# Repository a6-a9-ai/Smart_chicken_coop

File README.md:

# smartChicken: Multi-Sensor Environmental & Security System

A lightweight, event-driven application built on **Zephyr RTOS** for multi-sensor data collection and Bluetooth Low Energy (BLE) alert broadcasting.

## Project Structure
* **`soft_nRF`**: Core sensor hub firmware utilizing cooperative and preemptive workqueues to schedule non-blocking sensor sampling and manage UART/PWM peripherals.
* **`soft_nRF_R`**: Standalone receiver node logic that scans for specific broadcasting frames and drives physical LED indicators based on alert states.
* **`PCBs`**: Design files for 3 custom boards handling solar power adaptation, battery storage, and 3.3V/5V regulated power delivery.
* **`3D_prints`**: Mechanical manufacturing models, including a structural base support for a 24-cell PV solar panel.

---
<details>
  <summary> Power supply layout </summary>

</details>

<details>
  <summary> Receptor board layout </summary>

</details>

<details>
  <summary> Connector board layout </summary>

</details>

<details>
  <summary> Power supply routes </summary>

</details>

<details>
  <summary> Power supply 3D board </summary>

</details>

<details>
  <summary> Connector 3D board </summary>

</details>

<details>
  <summary> Receptor 3D board </summary>

</details>

## Technical Specifications

### 1. Concurrency Contexts (`main.c`)
The system offloads tasks to Zephyr's workqueue framework to avoid continuous thread shifting:
*   **`sensor_wq`**: Cooperative workqueue (Stack: 1024, Priority: 5) dedicated to regular, periodic sensor sampling routines.
*   **`critical_wq`**: Preemptive workqueue (Stack: 1024, Priority: -4) reserved for immediate actuator responses.

### 2. Peripheral & Sensor Matrix
*   **SCD30**: Interfaced via I2C (`DT_NODELABEL(scd30)`). It measures CO2, temperature, and humidity. Integrity is verified through a Sensirion-compliant polynomial `0x31` CRC-8 check.
*   **DHT11**: Connected via GPIO (`gpio0`, pin 4). Measures environmental metrics every 5000 ms using single-wire signaling.
*   **PIR Sensor**: Connected via GPIO (`gpio1`, pin 8). Polled asynchronously every 2500 ms to capture motion vectors.
*   **Photodiode**: Monitors ambient light variations.
*   **Fan Actuator**: Driven by hardware PWM (`DT_ALIAS(pwm_led0)`) with a baseline period of 40 µs.
*   **UART Host Link**: Mapped to `uart20` (RX: P1.05, TX: P1.04). Operates with a 4-byte receive buffer and a 1000 µs window timeout for ESP32 communications.

### 3. Thresholds & Control Hysteresis
*   **CO2 Threshold**: Registers an alert state if carbon dioxide levels exceed 1000.0 ppm.
*   **Fan & Thermal Management (`DHT11.c`)**:
    *   Turns **ON** (100% duty cycle) if Temperature > 23°C (`FAN_THRESHOLD_TEMP_SUP`).
    *   Turns **OFF** (0% duty cycle) when Temperature drops below 23°C.

### 4. Custom BLE Alert Protocol
The transmitting hub identifies itself as `"smartChicken"`. Discovered alerts modify a 1-byte payload packaged within a Custom Manufacturer Data sequence using Company ID `0x0D06`:

| Bit Index | Packet Macro Flag | Trigger Condition |
| :--- | :--- | :--- |
| **Bit 0** | `BLE_PAQUET_TEMP_BIT` | Temperature exceeds 23°C |
| **Bit 1** | `BLE_PAQUET_GAS_BIT` | SCD30 calculated CO2 exceeds 1000.0 ppm |
| **Bit 2** | `BLE_PAQUET_ATTACK_BIT` | Motion registered by the PIR sensor line |

The receiver application (`soft_nRF_R`) scans for this explicit frame, decodes the bit field state, and directly alters the status of `led0`, `led1`, and `led2`.

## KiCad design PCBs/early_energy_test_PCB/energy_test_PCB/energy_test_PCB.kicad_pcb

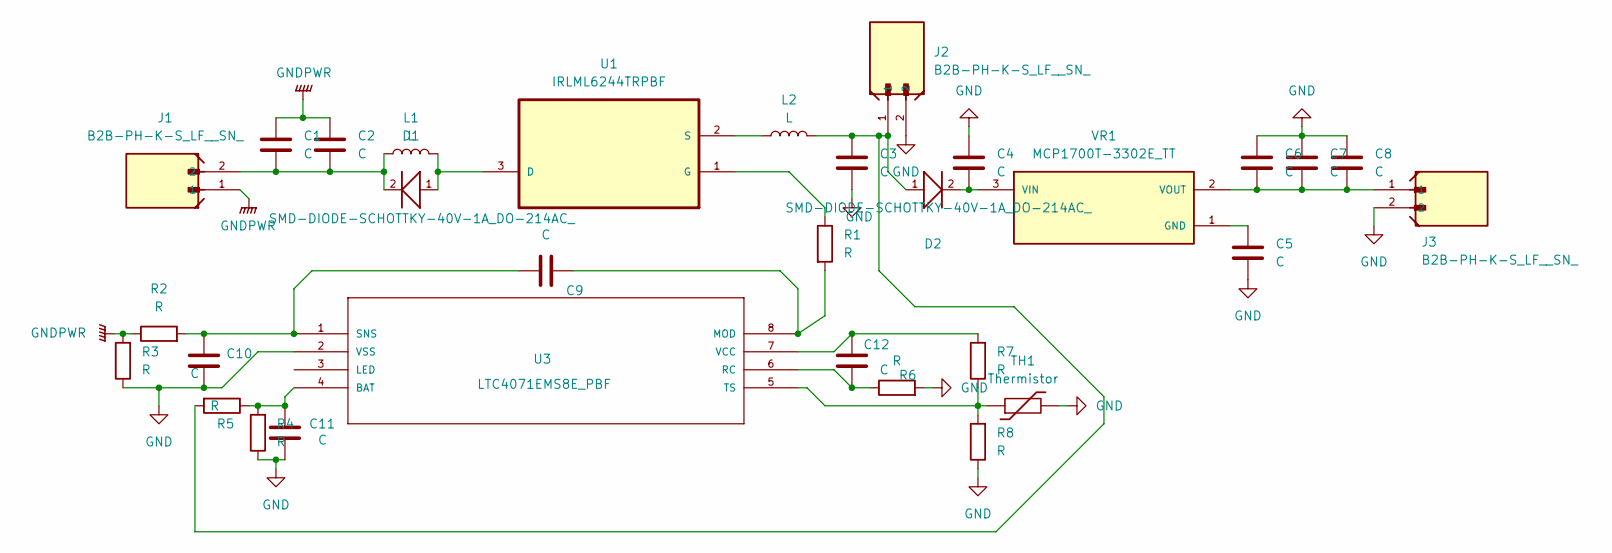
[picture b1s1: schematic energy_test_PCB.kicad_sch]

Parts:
C1, C2, C3, C4, C5, C6, C7, C8, C9, C10, C11, C12: C; R_Axial_DIN0207_L6.3mm_D2.5mm_P7.62mm_Horizontal
D1, D2: SMD-DIODE-SCHOTTKY-40V-1A_DO-214AC_; R_Axial_DIN0207_L6.3mm_D2.5mm_P7.62mm_Horizontal; MPN 1N5819
J1, J2, J3: B2B-PH-K-S_LF__SN_; JST_B2B-PH-K-S_LF__SN_
L1, L2: L; L_Radial_D12.0mm_P10.00mm_Neosid_SD12_style1
R1, R2, R3, R4, R5, R6, R7, R8: R; R_Axial_DIN0207_L6.3mm_D2.5mm_P7.62mm_Horizontal
TH1: Thermistor; R_Axial_DIN0207_L6.3mm_D2.5mm_P7.62mm_Horizontal
U1: IRLML6244TRPBF; SOT95P237X112-3N; MPN IRLML6244TRPBF
U3: LTC4071EMS8E_PBF; MSOP-8_MS; MANUFACTURER_PART_NUMBER ltc4071ems8e#pbf
VR1: MCP1700T-3302E_TT; SOT95P237X112-3N; PARTREV E

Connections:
GND: C3.2, C4.1, C5.2, C6.1, C7.1, C8.1, C10.1, C11.1, J2.2, J3.2, R3.1, R4.1, R6.2, R8.1, TH1.2, U3.2 (VSS)
GNDPWR: C1.1, C2.1, J1.1, R2.1, R3.2
unnamed: C1.2, C2.2, D1.2, J1.2, L1.1
unnamed: C3.1, D2.1, J2.1, L2.2, R5.2
unnamed: D1.1, L1.2, U1.3 (D)
unnamed: R1.1, U1.1 (G)
unnamed: L2.1, U1.2 (S)
unnamed: C11.2, R4.2, R5.1, U3.4 (BAT)
unnamed: C9.2, R1.2, U3.8 (MOD)
unnamed: C12.1, R6.1, U3.6 (RC)
unnamed: C9.1, C10.2, R2.2, U3.1 (SNS)
unnamed: R7.1, R8.2, TH1.1, U3.5 (TS)
unnamed: C12.2, R7.2, U3.7 (VCC)
unnamed: C5.1, VR1.1 (GND)
unnamed: C4.2, D2.2, VR1.3 (VIN)
unnamed: C6.2, C7.2, C8.2, J3.1, VR1.2 (VOUT)

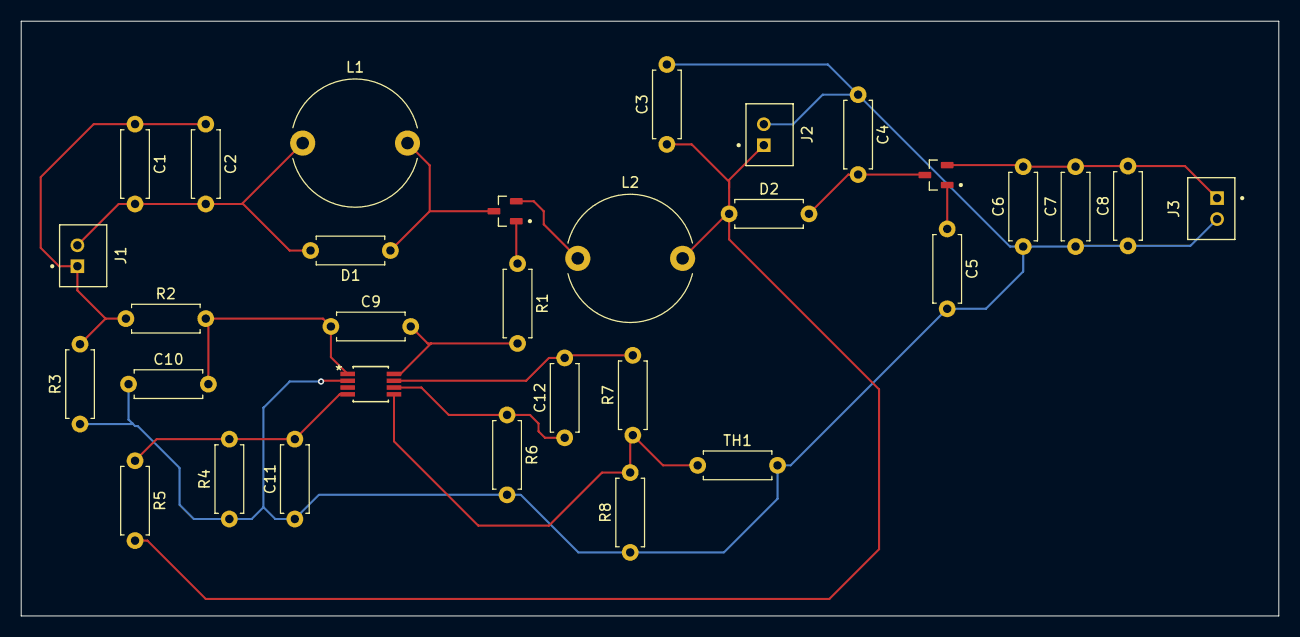
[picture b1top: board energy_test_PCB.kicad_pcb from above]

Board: 2 copper layers, 120.0 x 56.8 mm, 31 parts (0 on the bottom side), 16 nets.

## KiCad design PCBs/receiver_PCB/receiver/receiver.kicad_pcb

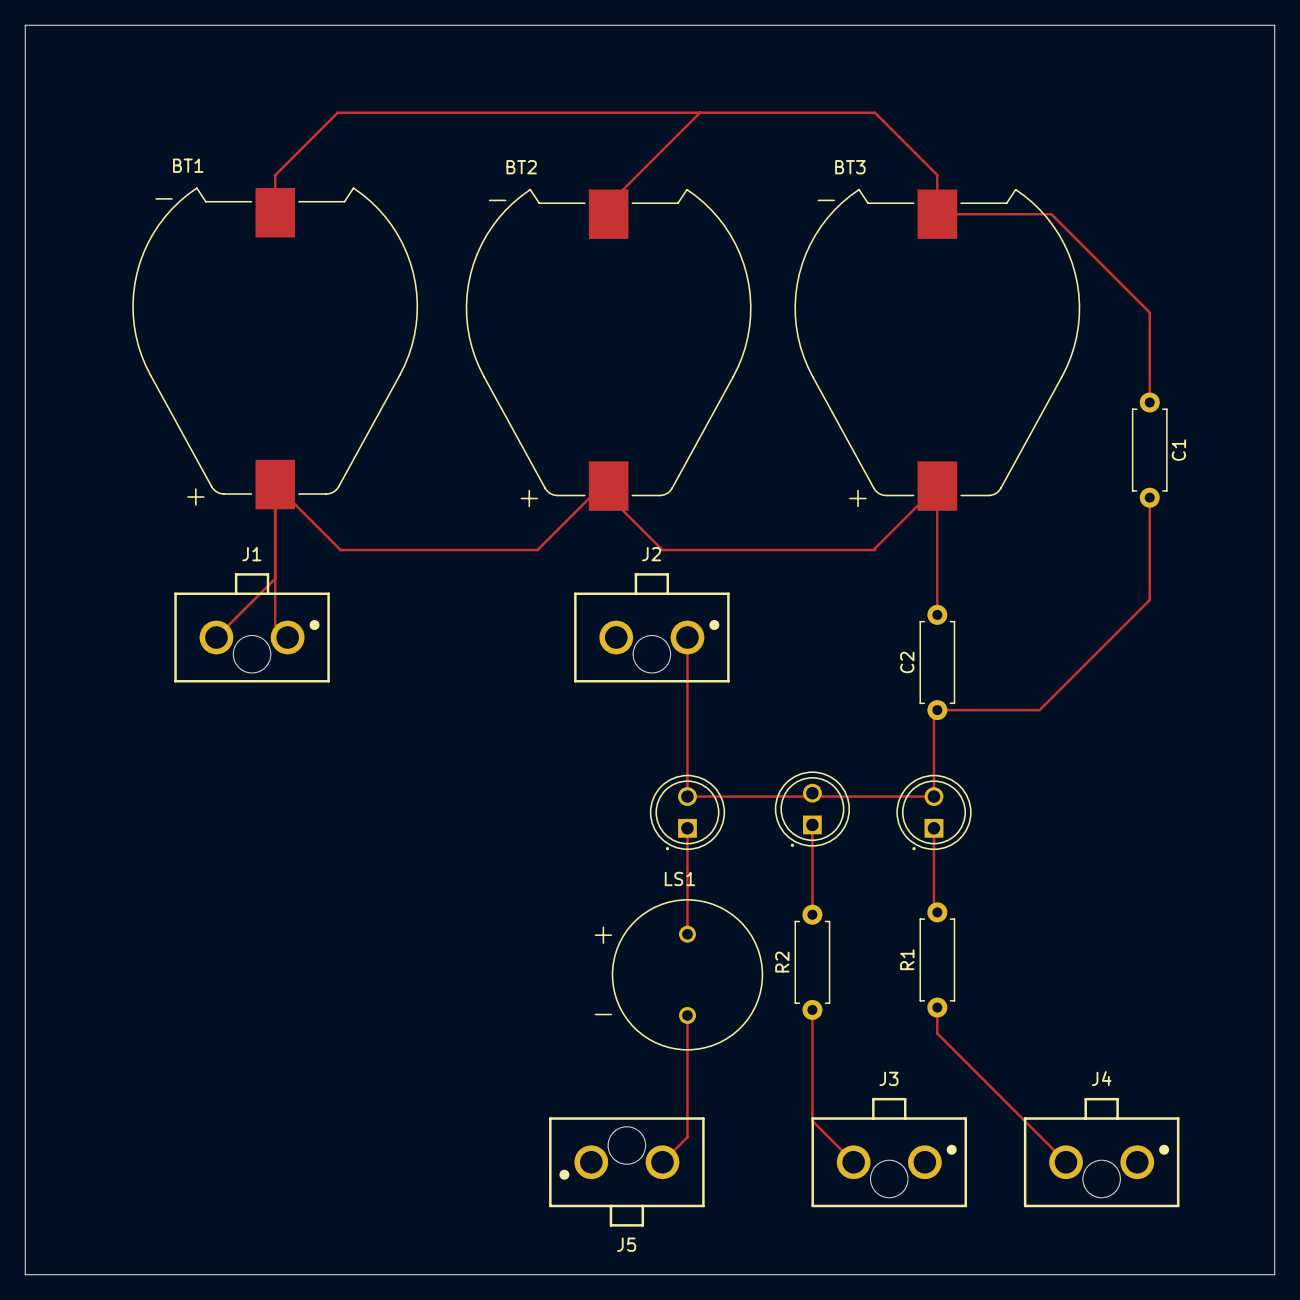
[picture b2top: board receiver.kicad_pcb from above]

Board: 2 copper layers, 100.0 x 100.0 mm, 16 parts (0 on the bottom side), 9 nets.

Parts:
BT1, BT2, BT3: 1062; BAT_1062
C1, C2: C; R_Axial_DIN0207_L6.3mm_D2.5mm_P7.62mm_Horizontal
D1, D2, D3: WP7113ID; LED_WP7113ID
J1, J2, J3, J4, J5: 6570XX140201_657002140201; 657002140201
LS1: AT-1224-TWT-R; XDCR_AT-1224-TWT-R
R1, R2: R; R_Axial_DIN0207_L6.3mm_D2.5mm_P7.62mm_Horizontal

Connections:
GND: BT1.P, BT2.P, BT3.P, C2.2, J1.1, J1.2
unnamed: BT1.N, BT2.N, BT3.N, C1.1
unnamed: C1.2, C2.1, D1.A, D2.A, D3.A, J2.1
unnamed: D1.C, R1.2
unnamed: D2.C, R2.2
unnamed: D3.C, LS1.P
unnamed: J3.2, R2.1
unnamed: J4.2, R1.1
unnamed: J5.2, LS1.N

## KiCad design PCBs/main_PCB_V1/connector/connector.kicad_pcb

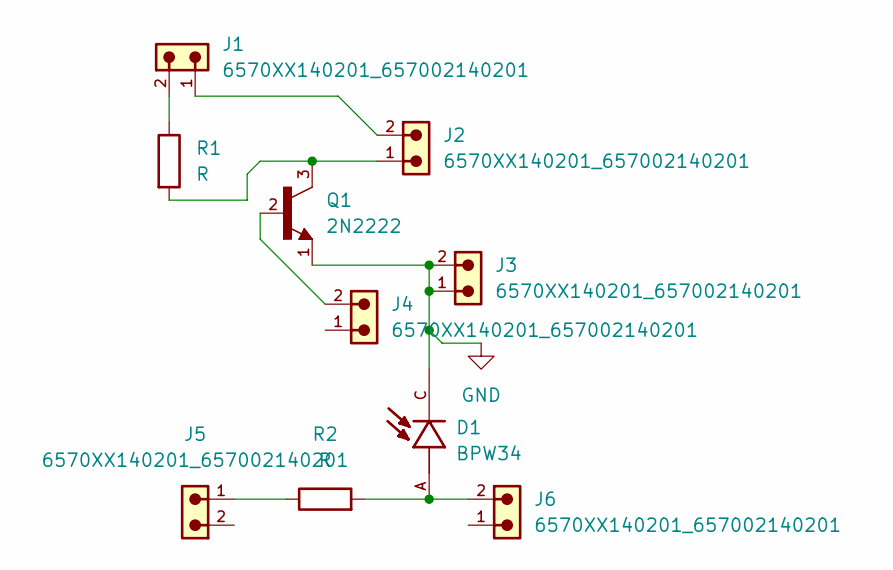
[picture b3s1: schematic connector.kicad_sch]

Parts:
D1: BPW34; DIO_BPW34; PARTREV 2.1
J1, J2, J3, J4, J5, J6: 6570XX140201_657002140201; 657002140201
Q1: 2N2222; TO127P584H533-3; PARTREV January 1989
R1, R2: R; R_Axial_DIN0207_L6.3mm_D2.5mm_P7.62mm_Horizontal

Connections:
GND: D1.C, J3.1, J3.2, Q1.1
unnamed: D1.A, J6.2, R2.2
unnamed: J1.1, J2.2
unnamed: J1.2, R1.1
unnamed: J2.1, Q1.3, R1.2
unnamed: J4.2, Q1.2
unnamed: J5.1, R2.1

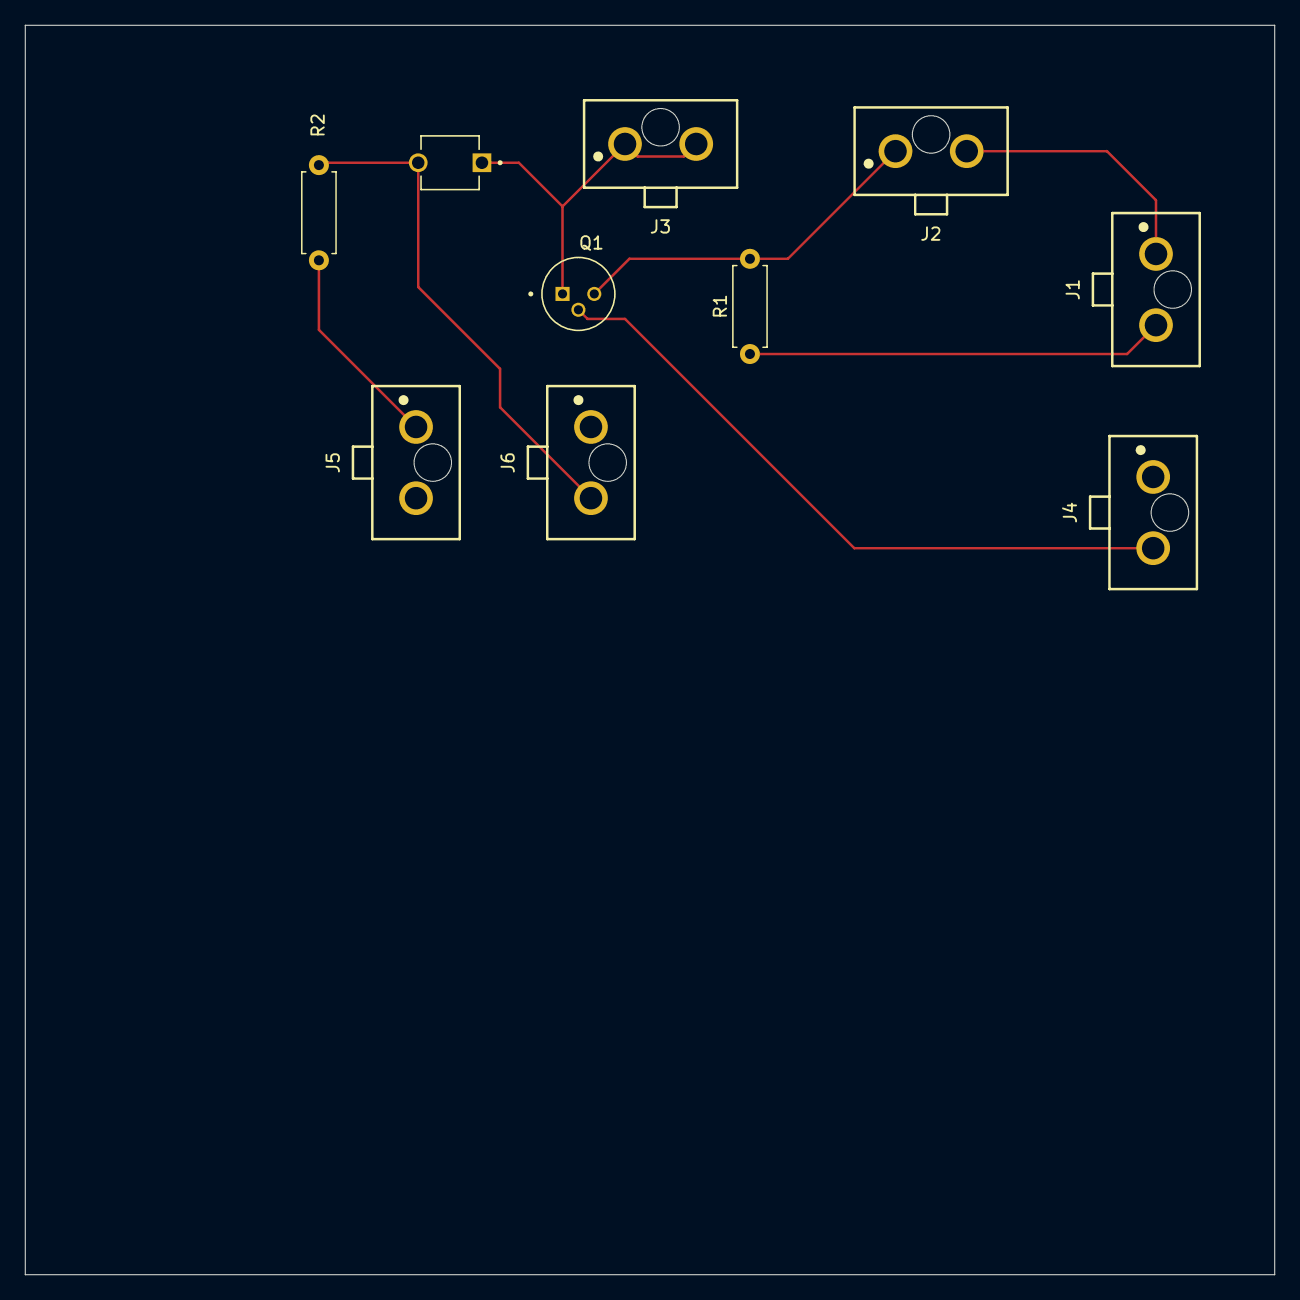
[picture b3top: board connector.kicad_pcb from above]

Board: 2 copper layers, 100.0 x 100.0 mm, 10 parts (0 on the bottom side), 7 nets.

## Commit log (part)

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2025-11-14 Add initial PCB footprints and zephyr code for DHT11 ans Fan_management
    Added KiCad symbols in PCB_footprints
    + PCB_footprints_save directories. Included simulation script
    + initial source files for nRF project.
    (the fan is on when temperature is over 23°C according to DHT11.
    Every process is processed through workqueues defined in main.c.
2025-11-14 Add PCB design + 3D print files
    Added support structure STL files for PV module.
    Included new PCB design for early energy test PCB.
    + footprints updates
2025-11-15 merging fan_control.c in DHT11.c
    merging fan_control.c in DHT11.c
    + workqueue structure for BLE alert
    + fan management optimisation
2025-11-17 clean update
    clean code update
2025-11-19 ble alerte update
    fixed an issue about wq_critical pausing, fixed by scheduling bt_le_adv_stop() through new ble_stop_alerte_temp_work
2025-11-21 + payload for BLE alert
    creating the 3-bits advertizing payload
    + function to update the payload and managing adv
    -suspicious : DHT11 stops sometimes
2026-01-04 Add receiver PCB files and update energy test PCB (V0)
    Added new receiver PCB design files, including footprints, symbols, 3D models, and project backups. Updated early energy test PCB files with detailed board layout and schematic content.
2026-01-08 add the 3rd pcb
    Added new connector footprints, symbols, and STEP models for 2N2222, 2N2222A, BPW34, and 657002140201 in main_PCB_V1. Created new connector PCB project files. Updated .gitignore to exclude new backup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
2026-01-09 Add soft_nRF_R project and update receiver PCB
    Added new soft_nRF_R firmware project with initial source files. Updated receiver PCB design to use Wurth Elektronik connectors, revised net assignments, and replaced legacy footprints. Adjusted .git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
2026-05-24 sender_code and receiver and readme
